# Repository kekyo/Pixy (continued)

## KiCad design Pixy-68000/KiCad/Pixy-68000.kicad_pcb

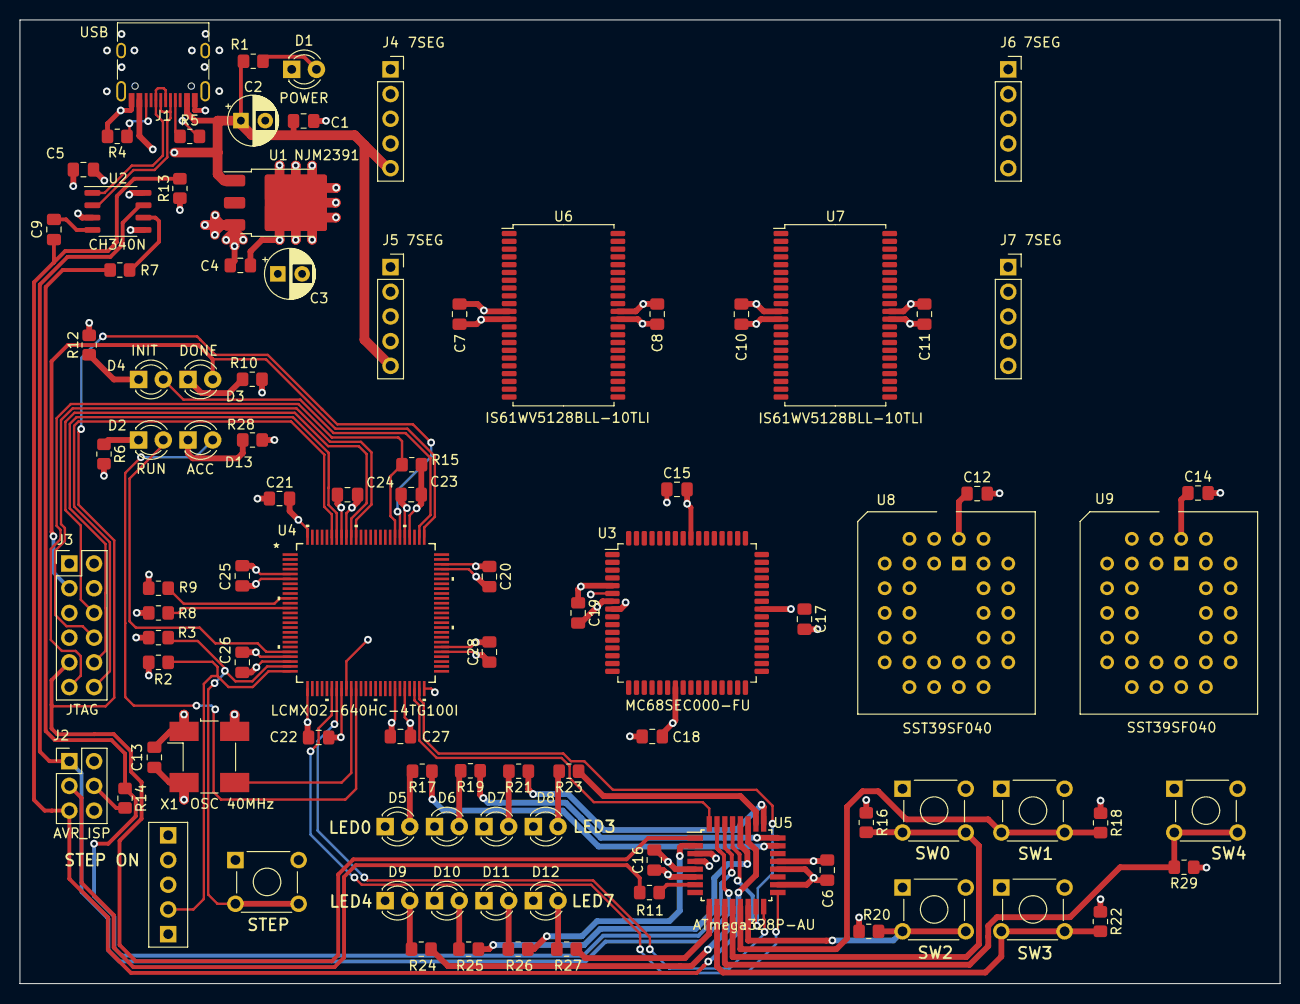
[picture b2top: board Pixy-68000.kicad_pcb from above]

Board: 4 copper layers, 129.5 x 99.1 mm, 94 parts (0 on the bottom side), 122 nets.

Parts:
C1, C4, C5, C6, C7, C8, C9, C10, C11, C12, C13, C14, C15, C16, C17, C18, C19, C20, C21, C22, C23, C24, C25, C26, C27, C28: 0.1u; C_0805_2012
C2, C3: 100u; CP_Radial_D5.0mm_P2.50mm
D1: POWER; LED_D3.0mm
D2: RUN; LED_D3.0mm
D3: DONE; LED_D3.0mm
D4: INIT; LED_D3.0mm
D5: LED0; LED_D3.0mm
D6: LED1; LED_D3.0mm
D7: LED2; LED_D3.0mm
D8: LED3; LED_D3.0mm
D9: LED4; LED_D3.0mm
D10: LED5; LED_D3.0mm
D11: LED6; LED_D3.0mm
D12: LED7; LED_D3.0mm
D13: ACC; LED_D3.0mm
J1: USB; USB_C_Receptacle_HRO_TYPE-C-31-M-12
J2: AVR_ISP; PinHeader_2x03_P2.54mm_Vertical
J3: JTAG; PinHeader_2x06_P2.54mm_Vertical
J4, J5, J6, J7: Socket5; PinSocket_1x05_P2.54mm_Vertical
R1, R6, R10, R12, R16, R17, R18, R19, R20, R21, R22, R23, R24, R25, R26, R27, R28, R29: 2k; R_0805_2012
R2, R3, R8, R9, R15: 1.5k; R_0805_2012
R4, R5: 5.1k; R_0805_2012
R7, R11, R14: 1k; R_0805_2012
R13: 10k; R_0805_2012
SW0: SW0; TactSwitch
SW1: SW1; TactSwitch
SW2: SW2; TactSwitch
SW3: SW3; TactSwitch
SW4: SW4; TactSwitch
SW_STEP1: STEP; TactSwitch
SW_STEPEN1: STEPEN; SW_Toggle_3P
U1: NJM2391; TO-252-3_TabPin4
U2: CH340N; SOP-8_3.9x4.9mm_P1.27mm
U3: MC68SEC000-FU
U4: LCMXO2-640HC-4TG100I; TQFP100_LAT-M
U5: ATmega328P-AU; TQFP-32_7x7mm_P0.8mm
U6, U7: IS61WV5128BLL-10TLI; TSOP-II-44_10.16x18.41mm_P0.8mm
U8, U9: SST39SF040; PLCC-32_THT-Socket
X1: X1; Oscillator_SMD_4Pin_7.0x5.0mm_HandSoldering

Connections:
/A0: U3.19 (A0), U4.37 (PB10B)
/A1: U3.20 (A1), U4.38 (PB10C/PCLKT2_1), U6.3 (A0), U7.3 (A0), U8.12 (A0), U9.12 (A0)
/A2: U3.21 (A2), U4.39 (PB10D/PCLKC2_1), U6.4 (A1), U7.4 (A1), U8.11 (A1), U9.11 (A1)
/A3: U3.22 (A3), U4.40 (PB12A), U6.5 (A2), U7.5 (A2), U8.10 (A2), U9.10 (A2)
/A4: U3.24 (A4), U4.41 (PB12B), U6.6 (A3), U7.6 (A3), U8.9 (A3), U9.9 (A3)
/A5: U3.25 (A5), U4.42 (PB12C), U6.7 (A4), U7.7 (A4), U8.8 (A4), U9.8 (A4)
/A6: U3.26 (A6), U4.43 (PB12D), U6.16 (A5), U7.16 (A5), U8.7 (A5), U9.7 (A5)
/A7: U3.27 (A7), U4.45 (PB14A), U6.17 (A6), U7.17 (A6), U8.6 (A6), U9.6 (A6)
/A8: U3.28 (A8), U4.47 (PB14B), U6.18 (A7), U7.18 (A7), U8.5 (A7), U9.5 (A7)
/A9: U3.29 (A9), U4.51 (PR7D), U6.19 (A8), U7.19 (A8), U8.27 (A8), U9.27 (A8)
/A10: U3.30 (A10), U4.52 (PR7C), U6.20 (A9), U7.20 (A9), U8.26 (A9), U9.26 (A9)
/A11: U3.31 (A11), U4.53 (PR7B), U6.26 (A10), U7.26 (A10), U8.23 (A10), U9.23 (A10)
/A12: U3.32 (A12), U4.54 (PR7A), U6.27 (A11), U7.27 (A11), U8.25 (A11), U9.25 (A11)
/A13: U3.33 (A13), U4.57 (PR6D), U6.28 (A12), U7.28 (A12), U8.4 (A12), U9.4 (A12)
/A14: U3.34 (A14), U4.58 (PR6C), U6.29 (A13), U7.29 (A13), U8.28 (A13), U9.28 (A13)
/A15: U3.35 (A15), U4.59 (PR6B), U6.30 (A14), U7.30 (A14), U8.29 (A14), U9.29 (A14)
/A16: U3.36 (A16), U4.60 (PR6A), U6.38 (A15), U7.38 (A15), U8.3 (A15), U9.3 (A15)
/A17: U3.37 (A17), U4.62 (PR5D/PCLKC1_0), U6.39 (A16), U7.39 (A16), U8.2 (A16), U9.2 (A16)
/A18: U3.38 (A18), U4.63 (PR5C/PCLKT1_0), U6.40 (A17), U7.40 (A17), U8.30 (A17), U9.30 (A17)
/A19: U3.39 (A19), U4.64 (PR5B), U6.41 (A18), U7.41 (A18), U8.1 (A18), U9.1 (A18)
/A20: U3.40 (A20), U4.65 (PR5A)
/A21: U3.42 (A21), U4.66 (PR3D)
/A22: U3.43 (A22), U4.67 (PR3C)
/A23: U3.44 (A23), U4.68 (PR3B)
/ACC: D13.2 (A), U4.36 (PB10A)
/CPUCLK: U3.6 (CLK), U4.34 (PB6C/PCLKT2_0)
/D0: U3.61 (D0), U4.99 (PT6A), U6.9 (I/O0)
/D1: U3.60 (D1), U4.98 (PT6B), U6.10 (I/O1)
/D2: U3.59 (D2), U4.97 (PT6C), U6.13 (I/O2)
/D3: U3.58 (D3), U4.96 (PT6D), U6.14 (I/O3)
/D4: U3.57 (D4), U4.88 (PT9A/PCLKT0_1), U6.31 (I/O4)
/D5: U3.55 (D5), U4.87 (PT9B/PCLKC0_1), U6.32 (I/O5)
/D6: U3.54 (D6), U4.86 (PT9C/SCL/PCLKT0_0), U6.35 (I/O6)
/D7: U3.53 (D7), U4.85 (PT9D/SDA/PCLKC0_0), U6.36 (I/O7)
/D8: U3.52 (D8), U4.84 (PT10A), U7.9 (I/O0)
/D9: U3.51 (D9), U4.83 (PT10B), U7.10 (I/O1)
/D10: U3.50 (D10), U4.78 (PT11A), U7.13 (I/O2)
/D11: U3.49 (D11), U4.75 (PR2A), U7.14 (I/O3)
/D12: U3.48 (D12), U4.74 (PR2B), U7.31 (I/O4)
/D13: U3.47 (D13), U4.71 (PR2C), U7.32 (I/O5)
/D14: U3.46 (D14), U4.70 (PR2D), U7.35 (I/O6)
/D15: U3.45 (D15), U4.69 (PR3A), U7.36 (I/O7)
/DONE: D3.2 (A), J3.3 (DONE), U4.76 (PT11D/DONE)
/FC0: U3.18 (FC0), U4.20 (PL7A/PCLKT3_0)
/FC1: U3.17 (FC1), U4.19 (PL6D)
/FC2: U3.16 (FC2), U4.18 (PL6C)
/INITN: D4.2 (A), U4.77 (PT11C/INITN)
/JTAGENB: J3.11 (VCC), R15.1, U4.82 (PT10C/JTAGENB)
/LED0: R17.1, U5.23 (PC0)
/LED1: R19.1, U5.24 (PC1)
/LED2: R21.1, U5.25 (PC2)
/LED3: R23.1, U5.26 (PC3)
/LED4: R24.1, U5.27 (PC4)
/LED5: R25.1, U5.28 (PC5)
/LED6: R26.1, U5.2 (PD4)
/LED7: R27.1, U5.9 (PD5)
/LEDDIO0: J4.1 (P0), U4.27 (PB4A/CSSPIN)
/LEDDIO1: J5.1 (P0), U4.28 (PB4B)
/LEDRCK: J4.3 (P2), J5.3 (P2), U4.30 (PB4D)
/LEDSCK: J4.2 (P1), J5.2 (P1), U4.29 (PB4C)
/MCLK: U4.35 (PB6D/PCLKC2_0), X1.3 (OUT)
/PROGRAMN: J3.9 (ISPEN_PROG), U4.81 (PT10D/PROGRAMN), U5.1 (PD3)
/REQINT: U4.48 (PB14C/SN), U5.32 (PD2)
/RUN: D2.2 (A), U4.21 (PL7B/PCLKC3_0)
/RXDAVR: R7.1, R14.1, U5.30 (PD0)
/R/W: U3.1 (R/W), U4.4 (PL2D/PCLKC3_2)
/SCK: R11.1, U5.7 (XTAL1/PB6)
/SPICLK: U4.31 (PB6A/MCLK/CCLK), U5.17 (PB5)
/SPISI: U4.49 (PB14D/SI/SISPI), U5.15 (PB3)
/SPISO: U4.32 (PB6B/SO/SPISO), U5.16 (PB4)
/TCK: J3.6 (TCK_SCLK), U4.91 (PT7C/TCK)
/TDI: J3.10 (TDI_SI), U4.94 (PT7B/TDI)
/TDO: J3.12 (TDO_SO), U4.95 (PT7A/TDO)
/TMS: J3.8 (TMS), U4.90 (PT7D/TMS)
/TXDAVR: J2.1 (MISO), U2.7 (RXD), U5.31 (PD1)
//AS: U3.62 (/AS), U4.1 (PL2A)
//AVEC: U3.11 (/AVEC), U4.13 (PL5B/PCLKC3_1)
//BERR: U3.12 (/BERR), U4.14 (PL5C)
//BG: U3.3 (/BG), U4.8 (PL3B)
//BR: U3.4 (/BR), U4.9 (PL3C)
//DTACK: U3.2 (/DTACK), U4.7 (PL3A)
//HALT: R8.2, U3.9 (/HALT), U4.12 (PL5A/PCLKT3_1)
//IPL0: U3.15 (/IPL0), U4.17 (PL6B)
//IPL1: U3.14 (/IPL1), U4.16 (PL6A)
//IPL2: U3.13 (/IPL2), U4.15 (PL5D)
//LDS: U3.64 (/LDS), U4.3 (PL2C/PCLKT3_2)
//OE: U6.37 (~OE), U7.37 (~OE), U8.24 (OE), U9.24 (OE)
//RESET: R9.2, U3.10 (/RESET), U4.10 (PL3D)
//RESETAVR: C9.2, J2.5 (/RESET), R13.2, U5.29 (~RESET/PC6)
//STEP: R3.2, SW_STEP1.2, U4.24 (PL7C)
//STEPEN: R2.2, SW_STEPEN1.1 (A), U4.25 (PL7D)
//SW0: R16.2, SW0.2, U5.12 (PB0)
//SW1: R18.2, SW1.2, U5.13 (PB1)
//SW2: R20.2, SW2.2, U5.14 (PB2)
//SW3: R22.2, SW3.2, U5.10 (PD6)
//SW4: R29.2, SW4.2, U5.11 (PD7)
//UDS: U3.63 (/UDS), U4.2 (PL2B)
//WE: U6.15 (~WE), U7.15 (~WE), U8.31 (PGM), U9.31 (PGM)
GND: C1.2, C2.2, C3.2, C4.2, C5.2, C6.2, C7.2, C8.2, C10.2, C11.2, C12.2, C13.2, C14.2, C15.2, C16.2, C17.2, C18.2, C19.2, C20.2, C21.2, C22.2, C23.2, C24.2, C25.2, C26.2, C27.2, C28.2, D1.1 (K), D5.1 (K), D6.1 (K), D7.1 (K), D8.1 (K), D9.1 (K), D10.1 (K), D11.1 (K), D12.1 (K), J1.A1 (GND), J1.A12 (GND), J1.B1 (GND), J1.B12 (GND), J1.S1 (SHIELD), J2.6 (GND), J3.5 (GND), J4.4 (P3), J5.4 (P3), J6.4 (P3), J7.4 (P3), R4.2, R5.2, R6.2, R10.2, R12.2, R15.2, R28.2, SW0.1, SW1.1, SW2.1, SW3.1, SW4.1, SW_STEP1.1, SW_STEPEN1.2 (B), U1.4 (GND), U2.3 (GND), U3.7 (GND), U3.23 (GND), U3.56 (GND), U4.6 (GND), U4.22 (GND), U4.33 (GND), U4.44 (GND), U4.56 (GND), U4.72 (GND), U4.79 (GND), U4.92 (GND), U5.3 (GND), U5.5 (GND), U5.21 (GND), U6.12 (GND), U6.34 (GND), U7.12 (GND), U7.34 (GND), U8.16 (GND), U9.16 (GND), X1.2 (GND)
unnamed: D1.2 (A), R1.2
unnamed: D2.1 (K), R6.1
unnamed: D3.1 (K), R10.1
unnamed: D4.1 (K), R12.1
unnamed: D5.2 (A), R17.2
unnamed: D6.2 (A), R19.2
unnamed: D7.2 (A), R21.2
unnamed: D8.2 (A), R23.2
unnamed: D9.2 (A), R24.2
unnamed: D10.2 (A), R25.2
unnamed: D11.2 (A), R26.2
unnamed: D12.2 (A), R27.2
unnamed: D13.1 (K), R28.1
unnamed: J1.A5 (CC1), R5.1
unnamed: J1.B5 (CC2), R4.1
unnamed: J2.4 (MOSI), R14.2
unnamed: J2.3 (SCK), R11.2
unnamed: R7.2, U2.6 (TXD)
unnamed: J1.A6 (D+), J1.B6 (D+), U2.1 (UD+)
unnamed: J1.A7 (D-), J1.B7 (D-), U2.2 (UD-)
unnamed: C9.1, U2.4 (~RTS)
VCC: C3.1, C4.1, C5.1, C6.1, C7.1, C8.1, C10.1, C11.1, C12.1, C13.1, C14.1, C15.1, C16.1, C17.1, C18.1, C19.1, C20.1, C21.1, C22.1, C23.1, C24.1, C25.1, C26.1, C27.1, C28.1, J2.2 (VCC), R2.1, R3.1, R8.1, R9.1, R13.1, R16.1, R18.1, R20.1, R22.1, R29.1, U1.3 (OUT), U2.8 (V3), U3.5 (VCC), U3.8 (MODE), U3.41 (VCC), U4.5 (VCCIO3), U4.23 (VCCIO3), U4.26 (VCCIO2), U4.46 (VCCIO2), U4.50 (VCC), U4.55 (VCCIO1), U4.73 (VCCIO1), U4.80 (VCCIO0), U4.93 (VCCIO0), U4.100 (VCC), U5.4 (VCC), U5.6 (VCC), U5.18 (AVCC), U5.20 (AREF), U6.11 (VDD), U6.33 (VDD), U7.11 (VDD), U7.33 (VDD), U8.32 (VCC), U9.32 (VCC), X1.1 (OE), X1.4 (Vcc)
VDD: C1.1, C2.1, J1.A4 (VBUS), J1.A9 (VBUS), J1.B4 (VBUS), J1.B9 (VBUS), J4.5 (P4), J5.5 (P4), R1.1, U1.1 (IN), U2.5 (VCC)

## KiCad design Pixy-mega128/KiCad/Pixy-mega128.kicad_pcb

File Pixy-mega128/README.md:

# Pixy-mega128

## Specification

* [ATMEL ATMega128-16AU](https://www.microchip.com/en-us/product/ATmega128A) (Simplest 48+ GPIO)
  * 16MHz externel XTAL.
  * 128KB Flash, 4KB SRAM, 4KB EEPROM included.
* USB 2.0 Type-C
  * Power distribution fixed +5V (not PD)
  * USB Serial connection by WCH CH340N (Optional)
* Enabled Arduino IDE with [MCUdude/MegaCore](https://github.com/MCUdude/MegaCore).
  * USB easy ready to run downloader.
  * With auto reset feature.
* PB5, PB6 and PB7 are assigned LEDs. (PB5 LED is MegaCore Boot indicator standard.)
* PE0 is TX, PE1 is RX and PB1 is SCK. These pins are set of ATMEL AVR ICE/ISP and UART interfaces.
  * ISP header is compatible for genuine [ATMEL AVR ICE/ISP](https://www.microchip.com/en-us/development-tool/atatmel-ice).
  * You have to use ATMEL AVR ICE/ISP on first time Arduino (MegaCore) firmware download.
  * UART header is requied only use for your own serial port interface instead of U3 (WCH CH340N).

## PCB (Pixy-mega128-0)

## Pinout (Pixy-mega128-0)

## Sample code

### Blinker

Blinker for Onboard LEDs (PB5, PB6 and PB7)

[Blinker](Blinker/): PlatformIO project.

```c
#include <Arduino.h>

int count = 0;

void setup() {
  Serial.begin(115200);
  Serial.println("setup()");
  
  pinMode(PIN_PB5, OUTPUT);
  pinMode(PIN_PB6, OUTPUT);
  pinMode(PIN_PB7, OUTPUT);
}

void loop() {
  Serial.println("Hello World! " + String(count));
  int v = count & 0x07;
  
  if (v & 0x01)
    digitalWrite(PIN_PB5, HIGH);
  else
    digitalWrite(PIN_PB5, LOW);

  if (v & 0x02)
    digitalWrite(PIN_PB6, HIGH);
  else
    digitalWrite(PIN_PB6, LOW);
  
  if (v & 0x04)
    digitalWrite(PIN_PB7, HIGH);
  else
    digitalWrite(PIN_PB7, LOW);

  delay(500);
  count++;
}
```

### Cheaper 7segment 8digits LED

Bought this LED module by: [0.36 inch 8digit 74HC595 version](https://www.ebay.com/itm/334240929966?var=543243005124)

```c
#include <Arduino.h>

#define DIO     PIN_PB2
#define SCLK    PIN_PB1
#define RCLK    PIN_PB3

static const byte digitPatterns[16] = {
  B11000000,  // 0
  B11111001,  // 1
  B10100100,  // 2
  B10110000,  // 3
  B10011001,  // 4
  B10010010,  // 5
  B10000010,  // 6
  B11111000,  // 7
  B10000000,  // 8
  B10010000,  // 9
  B10001000,  // a
  B10000011,  // b
  B11000110,  // c
  B10100001,  // d
  B10000110,  // e
  B10001110   // f
};

void setup() {
  pinMode(DIO, OUTPUT);
  pinMode(SCLK, OUTPUT);
  pinMode(RCLK, OUTPUT);

  digitalWrite(SCLK, HIGH);
  digitalWrite(RCLK, HIGH);
}

static void outputBits(byte value) {
  for (int j = 0; j < 8; j++) {
    digitalWrite(DIO, (value & 0x80) ? HIGH : LOW);
    digitalWrite(SCLK, LOW);
    digitalWrite(SCLK, HIGH);
    value <<= 1;
  }
}

static void flush() {
    digitalWrite(RCLK, LOW);
    digitalWrite(RCLK, HIGH);
}

static void output4Segments(uint16_t value, bool isHigh) {
  byte column = isHigh ? 0x80 : 0x08;
  for (int i = 0; i < 4; i++) {
    // Makes value bits
    byte v0 = digitPatterns[value & 0x0f];
    outputBits(v0);
    // Makes column bits
    outputBits(column);
    value >>= 4;
    column >>= 1;
    flush();
  }
}

static uint32_t value = 0;

void loop() {
  output4Segments((value >> 16) & 0xffffffff, true);
  output4Segments(value & 0xffffffff, false);

  outputBits(0);
  outputBits(0);
  flush();

  value++;
}
```

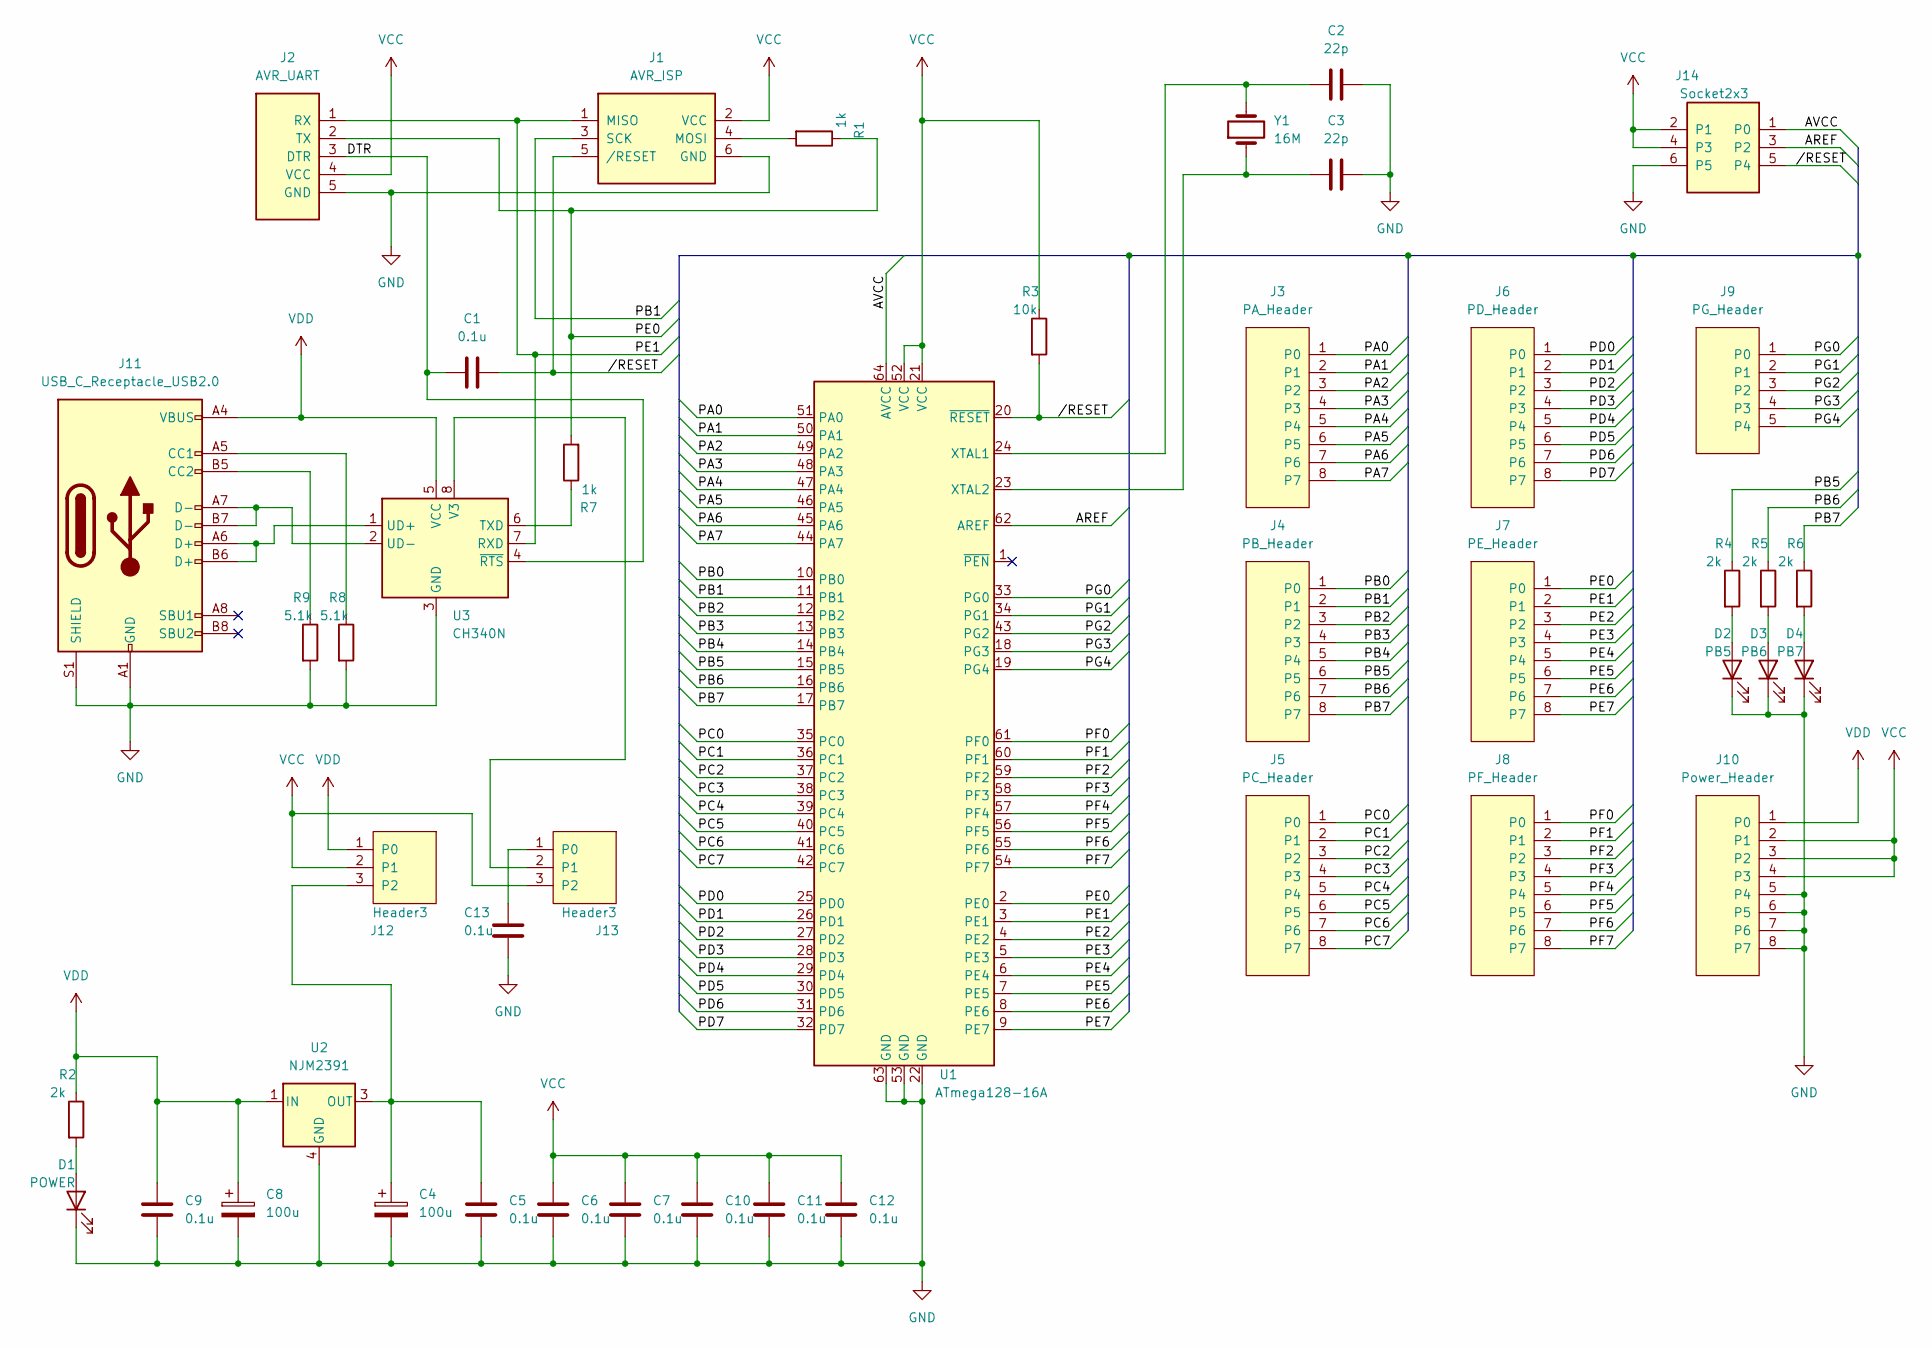
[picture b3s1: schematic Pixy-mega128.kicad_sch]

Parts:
C1, C5, C6, C7, C9, C10, C11, C12, C13: 0.1u; C_Disc_D4.3mm_W1.9mm_P5.00mm
C2, C3: 22p; C_Disc_D4.3mm_W1.9mm_P5.00mm
C4, C8: 100u; CP_Radial_D5.0mm_P2.50mm
D1: POWER; LED_D3.0mm
D2: PB5; LED_D3.0mm
D3: PB6; LED_D3.0mm
D4: PB7; LED_D3.0mm
J1: AVR_ISP; PinHeader_2x03_P2.54mm_Vertical
J2: AVR_UART; PinHeader_1x05_P2.54mm_Vertical
J3: PA_Header; PinHeader_1x08_P2.54mm_Vertical
J4: PB_Header; PinHeader_1x08_P2.54mm_Vertical
J5: PC_Header; PinHeader_1x08_P2.54mm_Vertical
J6: PD_Header; PinHeader_1x08_P2.54mm_Vertical
J7: PE_Header; PinHeader_1x08_P2.54mm_Vertical
J8: PF_Header; PinHeader_1x08_P2.54mm_Vertical
J9: PG_Header; PinSocket_1x05_P2.54mm_Vertical
J10: Power_Header; PinHeader_1x08_P2.54mm_Vertical
J11: USB_C_Receptacle_USB2.0; USB_C_Receptacle_HRO_TYPE-C-31-M-12
J12, J13: Header3; PinHeader_1x03_P2.54mm_Vertical
J14: Socket2x3; PinHeader_2x03_P2.54mm_Vertical
R1, R7: 1k; R_Axial_DIN0204_L3.6mm_D1.6mm_P2.54mm_Vertical
R2, R4, R5, R6: 2k; R_Axial_DIN0204_L3.6mm_D1.6mm_P2.54mm_Vertical
R3: 10k; R_Axial_DIN0204_L3.6mm_D1.6mm_P2.54mm_Vertical
R8, R9: 5.1k; R_Axial_DIN0204_L3.6mm_D1.6mm_P2.54mm_Vertical
U1: ATmega128-16A; QFP-64_AVR128
U2: NJM2391; TO-252-3_TabPin4
U3: CH340N; SOP-8_3.9x4.9mm_P1.27mm
Y1: 16M; Crystal_HC18-U_Vertical

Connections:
/AREF: J14.3 (P2), U1.62 (AREF)
/AVCC: J14.1 (P0), U1.64 (AVCC)
/DTR: C1.1, J2.3 (DTR), U3.4 (~RTS)
/PA0: J3.1 (P0), U1.51 (PA0)
/PA1: J3.2 (P1), U1.50 (PA1)
/PA2: J3.3 (P2), U1.49 (PA2)
/PA3: J3.4 (P3), U1.48 (PA3)
/PA4: J3.5 (P4), U1.47 (PA4)
/PA5: J3.6 (P5), U1.46 (PA5)
/PA6: J3.7 (P6), U1.45 (PA6)
/PA7: J3.8 (P7), U1.44 (PA7)
/PB0: J4.1 (P0), U1.10 (PB0)
/PB1: J1.3 (SCK), J4.2 (P1), U1.11 (PB1)
/PB2: J4.3 (P2), U1.12 (PB2)
/PB3: J4.4 (P3), U1.13 (PB3)
/PB4: J4.5 (P4), U1.14 (PB4)
/PB5: J4.6 (P5), R4.1, U1.15 (PB5)
/PB6: J4.7 (P6), R5.1, U1.16 (PB6)
/PB7: J4.8 (P7), R6.1, U1.17 (PB7)
/PC0: J5.1 (P0), U1.35 (PC0)
/PC1: J5.2 (P1), U1.36 (PC1)
/PC2: J5.3 (P2), U1.37 (PC2)
/PC3: J5.4 (P3), U1.38 (PC3)
/PC4: J5.5 (P4), U1.39 (PC4)
/PC5: J5.6 (P5), U1.40 (PC5)
/PC6: J5.7 (P6), U1.41 (PC6)
/PC7: J5.8 (P7), U1.42 (PC7)
/PD0: J6.1 (P0), U1.25 (PD0)
/PD1: J6.2 (P1), U1.26 (PD1)
/PD2: J6.3 (P2), U1.27 (PD2)
/PD3: J6.4 (P3), U1.28 (PD3)
/PD4: J6.5 (P4), U1.29 (PD4)
/PD5: J6.6 (P5), U1.30 (PD5)
/PD6: J6.7 (P6), U1.31 (PD6)
/PD7: J6.8 (P7), U1.32 (PD7)
/PE0: J2.2 (TX), J7.1 (P0), R1.1, R7.2, U1.2 (PE0)
/PE1: J1.1 (MISO), J2.1 (RX), J7.2 (P1), U1.3 (PE1), U3.7 (RXD)
/PE2: J7.3 (P2), U1.4 (PE2)
/PE3: J7.4 (P3), U1.5 (PE3)
/PE4: J7.5 (P4), U1.6 (PE4)
/PE5: J7.6 (P5), U1.7 (PE5)
/PE6: J7.7 (P6), U1.8 (PE6)
/PE7: J7.8 (P7), U1.9 (PE7)
/PF0: J8.1 (P0), U1.61 (PF0)
/PF1: J8.2 (P1), U1.60 (PF1)
/PF2: J8.3 (P2), U1.59 (PF2)
/PF3: J8.4 (P3), U1.58 (PF3)
/PF4: J8.5 (P4), U1.57 (PF4)
/PF5: J8.6 (P5), U1.56 (PF5)
/PF6: J8.7 (P6), U1.55 (PF6)
/PF7: J8.8 (P7), U1.54 (PF7)
/PG0: J9.1 (P0), U1.33 (PG0)
/PG1: J9.2 (P1), U1.34 (PG1)
/PG2: J9.3 (P2), U1.43 (PG2)
/PG3: J9.4 (P3), U1.18 (PG3)
/PG4: J9.5 (P4), U1.19 (PG4)
//RESET: C1.2, J1.5 (/RESET), J14.5 (P4), R3.2, U1.20 (~RESET)
GND: C2.2, C3.2, C4.2, C5.2, C6.2, C7.2, C8.2, C9.2, C10.2, C11.2, C12.2, C13.2, D1.1 (K), D2.1 (K), D3.1 (K), D4.1 (K), J1.6 (GND), J2.5 (GND), J10.5 (P4), J10.6 (P5), J10.7 (P6), J10.8 (P7), J11.A1 (GND), J11.A12 (GND), J11.B1 (GND), J11.B12 (GND), J11.S1 (SHIELD), J14.6 (P5), R8.2, R9.2, U1.22 (GND), U1.53 (GND), U1.63 (GND), U2.4 (GND), U3.3 (GND)
unnamed: D1.2 (A), R2.2
unnamed: D2.2 (A), R4.2
unnamed: D3.2 (A), R5.2
unnamed: D4.2 (A), R6.2
unnamed: J1.4 (MOSI), R1.2
unnamed: J11.A5 (CC1), R8.1
unnamed: J11.B5 (CC2), R9.1
unnamed: C4.1, C5.1, J12.3 (P2), U2.3 (OUT)
unnamed: C13.1, J13.1 (P0)
unnamed: J13.2 (P1), U3.8 (V3)
unnamed: C2.1, U1.24 (XTAL1), Y1.2
unnamed: C3.1, U1.23 (XTAL2), Y1.1
unnamed: R7.1, U3.6 (TXD)
unnamed: J11.A6 (D+), J11.B6 (D+), U3.1 (UD+)
unnamed: J11.A7 (D-), J11.B7 (D-), U3.2 (UD-)
VCC: C6.1, C7.1, C10.1, C11.1, C12.1, J1.2 (VCC), J2.4 (VCC), J10.2 (P1), J10.3 (P2), J10.4 (P3), J12.2 (P1), J13.3 (P2), J14.2 (P1), J14.4 (P3), R3.1, U1.21 (VCC), U1.52 (VCC)
VDD: C8.1, C9.1, J10.1 (P0), J11.A4 (VBUS), J11.A9 (VBUS), J11.B4 (VBUS), J11.B9 (VBUS), J12.1 (P0), R2.1, U2.1 (IN), U3.5 (VCC)

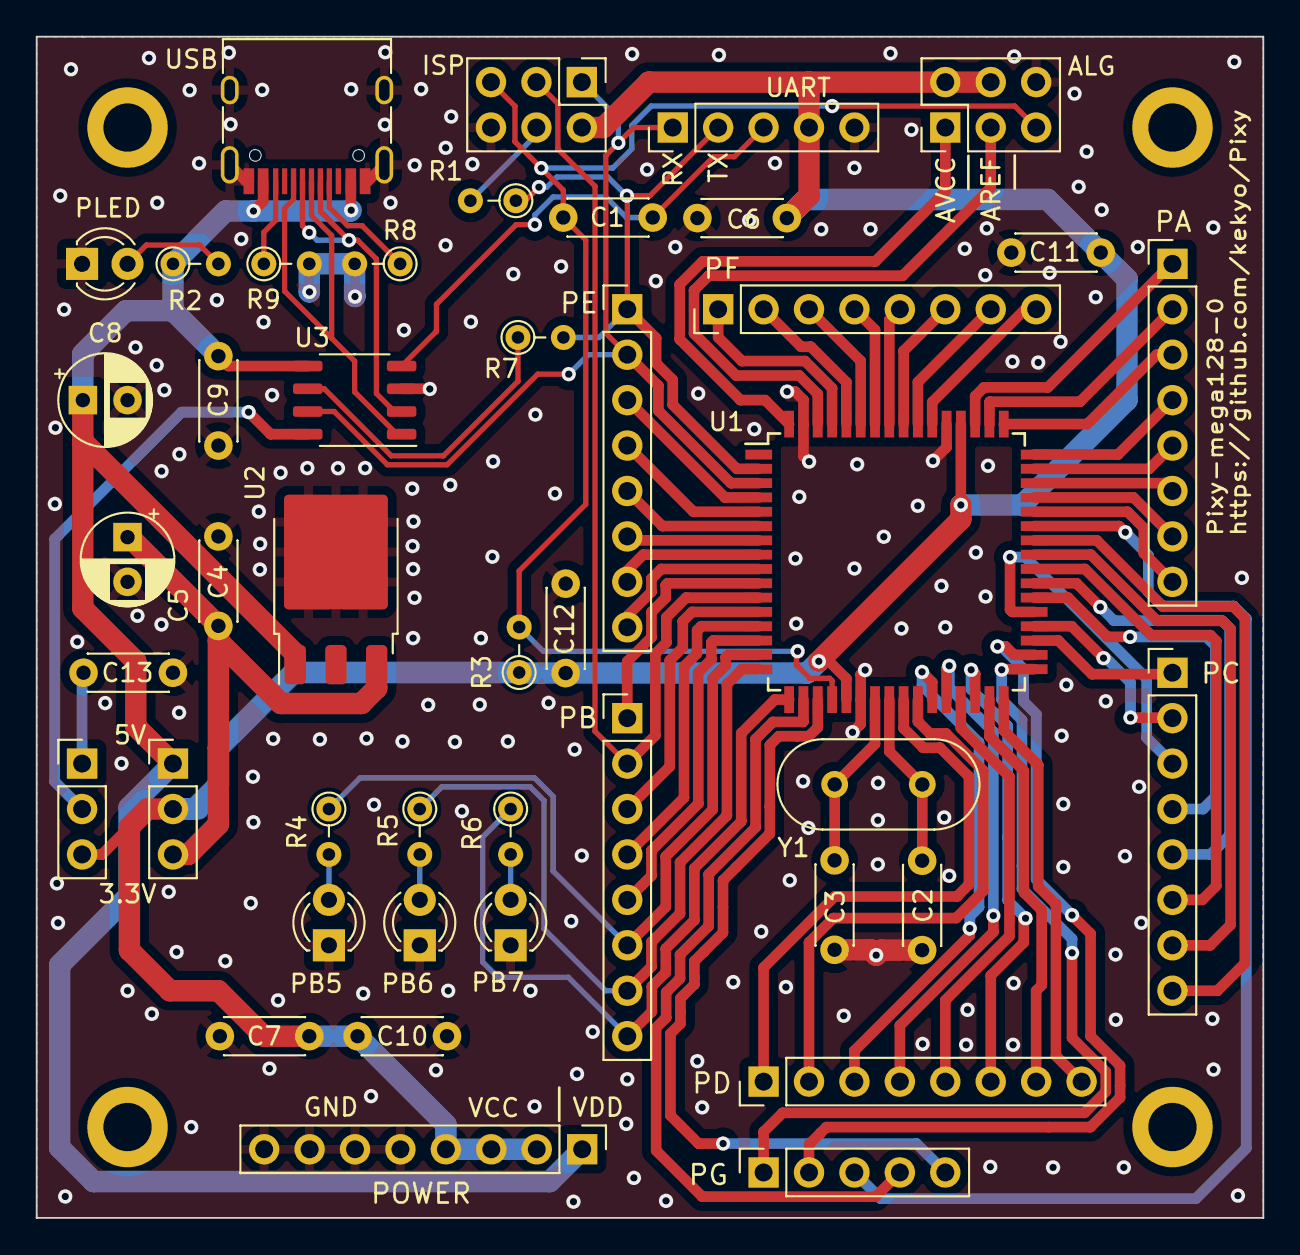
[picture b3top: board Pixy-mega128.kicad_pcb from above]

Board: 2 copper layers, 68.6 x 66.0 mm, 48 parts (0 on the bottom side), 75 nets.

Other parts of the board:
REF1, REF2, REF3, REF4: MountingHole_2.7mm_M2.5_ISO7380_Pad

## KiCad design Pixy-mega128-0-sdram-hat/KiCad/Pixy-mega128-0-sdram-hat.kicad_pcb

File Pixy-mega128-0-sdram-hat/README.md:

# Pixy-mega128-sdram-hat

## Specification

* SDRAM hat for Pixy-mega128-0
* EXPERIMENTAL circuit board, designed for learning SDRAM.
  * Not suitable for application use because Arduino cannot control it at a practical level.
  * Lack of any capacitors and position is undesirable. Therefore, high-speed access is not possible.

TODO:

## PCB (Pixy-mega128-0)

## Sample code

TODO:

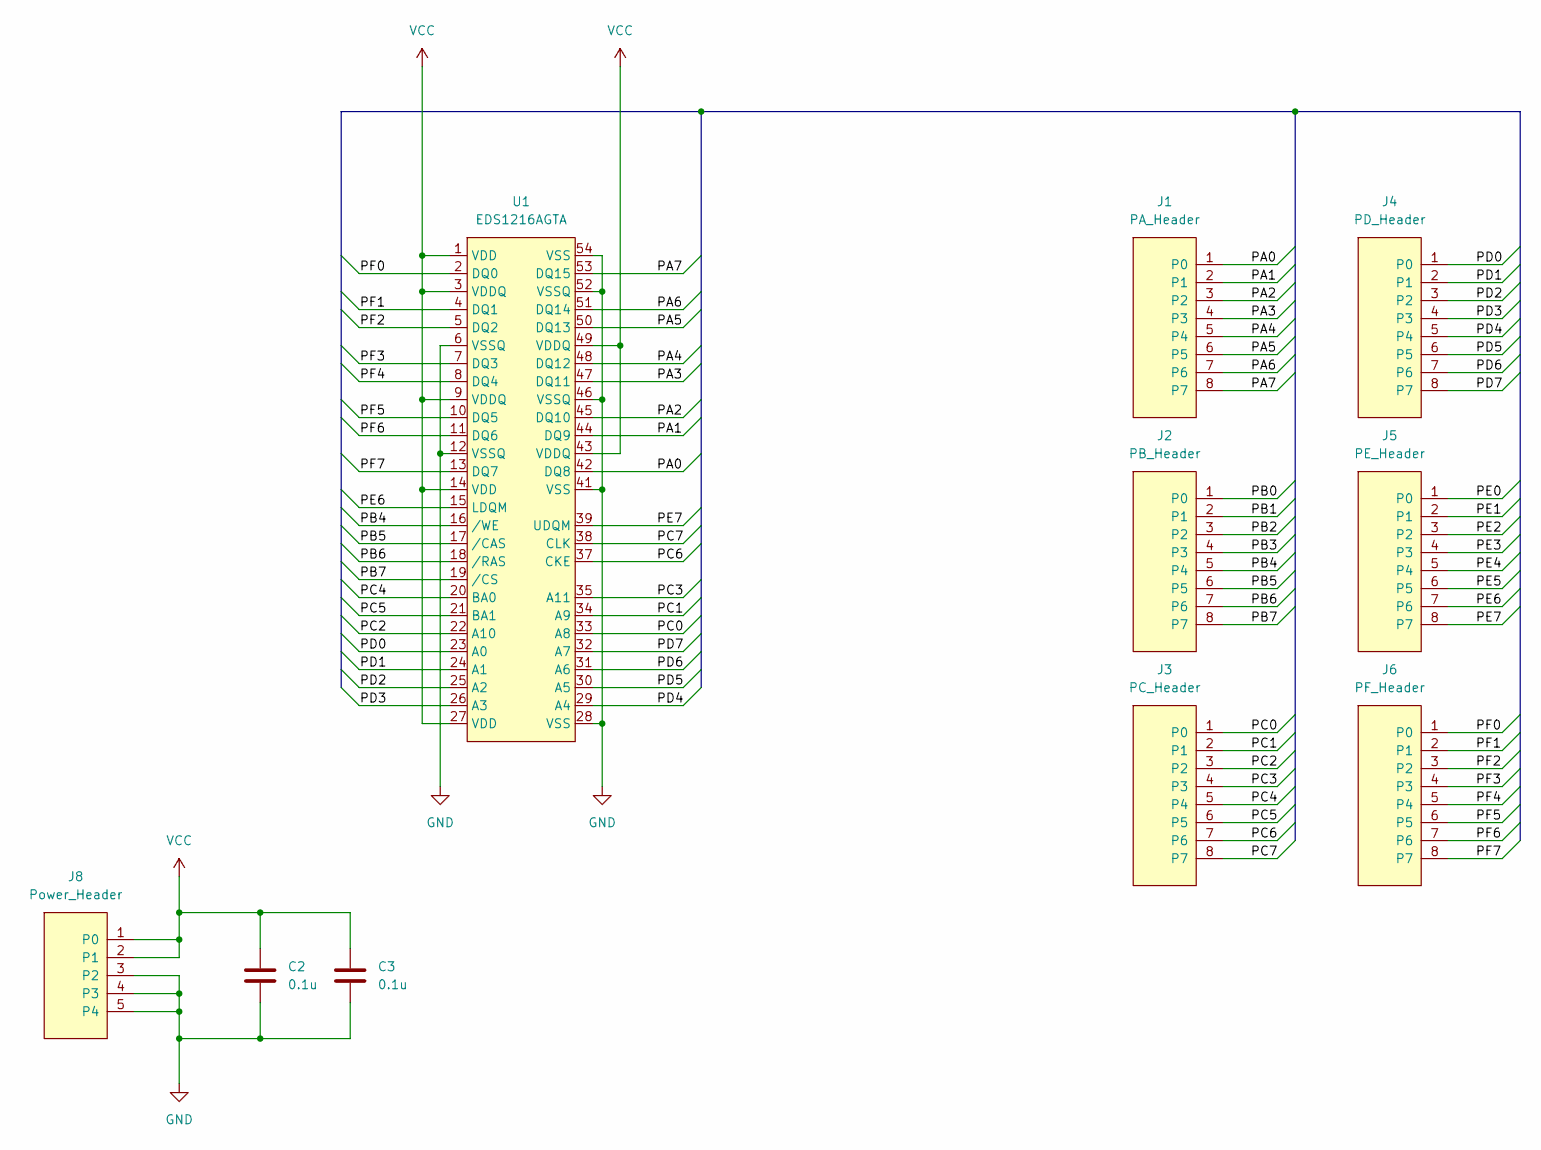
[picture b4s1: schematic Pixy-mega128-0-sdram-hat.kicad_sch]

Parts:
C2, C3: 0.1u; C_Disc_D4.3mm_W1.9mm_P5.00mm
J1: PA_Header; PinHeader_1x08_P2.54mm_Vertical
J2: PB_Header; PinHeader_1x08_P2.54mm_Vertical
J3: PC_Header; PinHeader_1x08_P2.54mm_Vertical
J4: PD_Header; PinHeader_1x08_P2.54mm_Vertical
J5: PE_Header; PinHeader_1x08_P2.54mm_Vertical
J6: PF_Header; PinHeader_1x08_P2.54mm_Vertical
J8: Power_Header; PinSocket_1x05_P2.54mm_Vertical
U1: EDS1216AGTA

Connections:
/PA0: J1.1 (P0), U1.42 (DQ8)
/PA1: J1.2 (P1), U1.44 (DQ9)
/PA2: J1.3 (P2), U1.45 (DQ10)
/PA3: J1.4 (P3), U1.47 (DQ11)
/PA4: J1.5 (P4), U1.48 (DQ12)
/PA5: J1.6 (P5), U1.50 (DQ13)
/PA6: J1.7 (P6), U1.51 (DQ14)
/PA7: J1.8 (P7), U1.53 (DQ15)
/PB0: J2.1 (P0)
/PB1: J2.2 (P1)
/PB2: J2.3 (P2)
/PB3: J2.4 (P3)
/PB4: J2.5 (P4), U1.16 (/WE)
/PB5: J2.6 (P5), U1.17 (/CAS)
/PB6: J2.7 (P6), U1.18 (/RAS)
/PB7: J2.8 (P7), U1.19 (/CS)
/PC0: J3.1 (P0), U1.33 (A8)
/PC1: J3.2 (P1), U1.34 (A9)
/PC2: J3.3 (P2), U1.22 (A10)
/PC3: J3.4 (P3), U1.35 (A11)
/PC4: J3.5 (P4), U1.20 (BA0)
/PC5: J3.6 (P5), U1.21 (BA1)
/PC6: J3.7 (P6), U1.37 (CKE)
/PC7: J3.8 (P7), U1.38 (CLK)
/PD0: J4.1 (P0), U1.23 (A0)
/PD1: J4.2 (P1), U1.24 (A1)
/PD2: J4.3 (P2), U1.25 (A2)
/PD3: J4.4 (P3), U1.26 (A3)
/PD4: J4.5 (P4), U1.29 (A4)
/PD5: J4.6 (P5), U1.30 (A5)
/PD6: J4.7 (P6), U1.31 (A6)
/PD7: J4.8 (P7), U1.32 (A7)
/PE0: J5.1 (P0)
/PE1: J5.2 (P1)
/PE2: J5.3 (P2)
/PE3: J5.4 (P3)
/PE4: J5.5 (P4)
/PE5: J5.6 (P5)
/PE6: J5.7 (P6), U1.15 (LDQM)
/PE7: J5.8 (P7), U1.39 (UDQM)
/PF0: J6.1 (P0), U1.2 (DQ0)
/PF1: J6.2 (P1), U1.4 (DQ1)
/PF2: J6.3 (P2), U1.5 (DQ2)
/PF3: J6.4 (P3), U1.7 (DQ3)
/PF4: J6.5 (P4), U1.8 (DQ4)
/PF5: J6.6 (P5), U1.10 (DQ5)
/PF6: J6.7 (P6), U1.11 (DQ6)
/PF7: J6.8 (P7), U1.13 (DQ7)
GND: C2.2, C3.2, J8.3 (P2), J8.4 (P3), J8.5 (P4), U1.6 (VSSQ), U1.12 (VSSQ), U1.28 (VSS), U1.41 (VSS), U1.46 (VSSQ), U1.52 (VSSQ), U1.54 (VSS)
VCC: C2.1, C3.1, J8.1 (P0), J8.2 (P1), U1.1 (VDD), U1.3 (VDDQ), U1.9 (VDDQ), U1.14 (VDD), U1.27 (VDD), U1.43 (VDDQ), U1.49 (VDDQ)

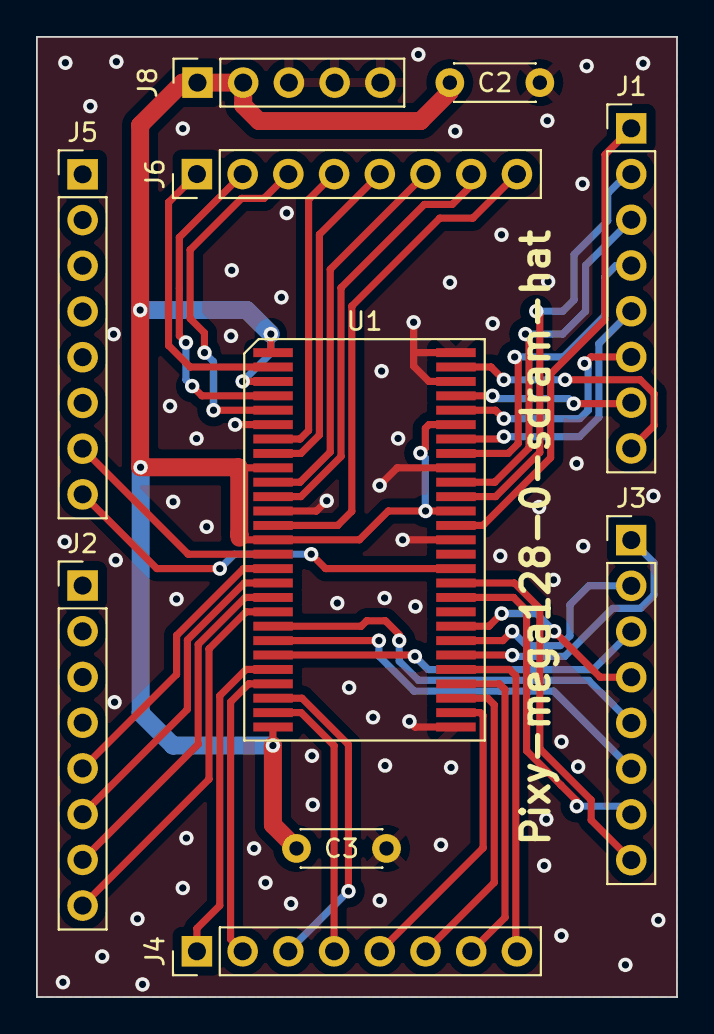
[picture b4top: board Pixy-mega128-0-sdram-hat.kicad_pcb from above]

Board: 2 copper layers, 35.6 x 53.3 mm, 10 parts (0 on the bottom side), 40 nets.

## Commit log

2023-10-29 Initial commit with Pixy-mega128-0
2023-10-29 Refactored directory structure.
2023-10-29 Added Pixy-mega128-0-sdram-hat.
2023-10-31 Updated readme.
2023-11-04 Fixed lacking C3.
2023-11-12 Hand routed basic connections.
2023-11-19 Completed artwork 68000-0.
2023-11-19 Added Pixy-mega128-0 blinker PlatformIO project.
2023-11-19 Initial commit for sdram-hat.
2023-11-21 Succeeded 1word read-write access.
2023-11-22 Improved controlling for SDRAM with bitbang.
2023-11-25 Added 68000-0 readme.
2023-11-25 Fixed bootloading JTAG signal lines on ATMega328P.
2023-11-25 Added errata information for MiniCore bootloader.
2023-11-26 Added PlatformIO based test code (WIP).
2023-11-26 Fixed JTAG pin header assignment.
2023-11-26 Refactored.
2023-11-26 Added diamond fpga project.
2023-11-26 Improved SEC68SEC000 pad length.
2023-11-27 Added ClockDivider
2023-11-27 Improved JTAG stability.
2023-11-27 Implemented initiator for dummy acknowledge.
2023-11-29 Turned negative signal symbols.
2023-11-29 Added looper test code.
2023-11-29 Bit changed.
2023-12-02 Added errara2 information.
    Fixed missing SPISS signal.
2023-12-03 Enabled stepper control.
2023-12-03 Fixed monitoring bit order.
2023-12-03 Totally checked booting from flash rom.
2023-12-03 Splitted both 0 and 1 version.
2023-12-08 Removed -0 gerber on -1 directory.
2023-12-08 Added memory selector headers.
2023-12-08 Implemented output signal on SPI.
2023-12-08 Implemented address decoder.
2023-12-08 Adjusted CPU clock speed to 0.5MHz.
2023-12-09 Implemented LED blinker.
2023-12-09 Implemented SRAM checker.
2023-12-10 Fixed exchanged RAM/PROM selector.
2023-12-10 Improved test indicator.
2023-12-10 Improved SRAM checker.
2023-12-10 Splitted SRAM checker.
2023-12-12 Implemented switch to LED.
2023-12-12 Switched to little endian and LSB first format on the SPI.
2023-12-12 Multiplexed I/O port bits.
2023-12-16 Changed synchronize-based logic.
2023-12-18 Added uart bridge (sender).
2023-12-19 Implemented uart receiver.
2023-12-20 Changed 7segment driving with timer interruption.
2023-12-21 Added /OE pullup register.
2023-12-21 Finalized Pixy-68000-1 with gerber data.
2023-12-22 Made bit-banning 7seg led driver.
2023-12-22 Improved uart echo back cycle cost.
2023-12-23 Enabled bus error.
2023-12-28 Implemented UART receive interrupt.
2023-12-29 Implemented UART send interrupt.
2023-12-29 Implemented free running counter and timer interrupt.
2024-01-02 Fixed sram_checker to apply newer signal port spec.
2024-01-02 Fixed did not assert DTACK when read timer counter port.
2024-01-03 Fixed invalid encoding for interrupt level bits.
2024-01-05 Fixed ram initialization.
2024-01-06 Partially supported C++.
2024-01-07 Tested printf/scanf.
2024-01-07 Added Lua-5.4.6 source.
2024-01-08 Moved to GitLab.
2024-01-08 Ported Lua shell.
2024-01-08 Enabled echo back for Lua shell.
2024-01-08 Re-enabled bus error.
2024-12-06 Improved lua shell interactivity.
2024-12-06 Initial Duktape implementation.
2024-12-29 Duktape pure REPL implementation.
2025-02-27 Implemented 68020 schematic.
2025-02-27 Changed MachXO2 footprint.
2025-02-27 Fixed minor footprint issue.
